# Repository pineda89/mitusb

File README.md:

# mitusb

A USB bridge for Teensy 4.1 that sits between a mouse, keyboard or gamepad and the computer. Connect the device to J6 and the computer to the micro-USB port. At startup, the board copies the device's USB identity and descriptors and then passes everything through in both directions. If there is nothing it can copy, it becomes a generic mouse.

The device works without Ethernet. With a mouse, the network client can also read events and send pointer commands; keyboards and gamepads are passed through untouched. Use a trusted network because the UDP protocol has no authentication. [Profiles, limits, and hardware checks](firmware/README.md)

## Build, test, and upload

Install PlatformIO Core and make sure `pio` is on your PATH. The first build downloads the toolchain and libraries. GNU Make is optional. The client requires Python 3.7 or later. You can run the native tests and build the firmware without a board.

Run the relevant command from the repository root.

```sh
make test    # Run the native tests
make         # Build the firmware
make upload  # Build and flash the board
make clean   # Remove the Teensy build output
```

The build produces `firmware/.pio/build/teensy41/firmware.hex`. Keep the device connected to J6 during restart so the firmware can capture its descriptors. If the loader cannot find the Teensy, press its **Program** button once.

The equivalent PlatformIO commands run from the firmware directory.

```sh
cd firmware
pio test -e native
pio run -e teensy41
pio run -e teensy41 -t upload
pio run -e teensy41 -t clean
```

## Directories

| Directory | Contents |
|---|---|
| [firmware/](firmware/) | Firmware, UDP protocol, and hardware checks |
| [client/](client/) | Command-line client and usage examples |
| [hardware/](hardware/) | KiCad project and board fabrication files |

## License

The project uses the [MIT License](LICENSE). The third-party KiCad libraries have [separate terms](hardware/README.md).

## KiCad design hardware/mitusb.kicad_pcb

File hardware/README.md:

# hardware

Carrier PCB for the Teensy 4.1, designed in KiCad 9.

## Contents

| Path | What |
|---|---|
| `mitusb.kicad_pro` | KiCad project (schematic + PCB) |
| `library/` | Project-local symbols, footprints and 3D models |
| `production/Gerber.zip` | Gerbers and drill files |
| `production/BOM.csv` | Bill of materials with LCSC part numbers |
| `production/mitusb-all-pos.csv` | Pick-and-place positions |
| `renders/` | Renders of the bare PCB and with the Teensy fitted |
| `enclosure/mitusb-case.scad` | Parametric OpenSCAD enclosure: base and flat lid, four M3 screws |
| `enclosure/mitusb-base.stl`, `enclosure/mitusb-lid.stl` | Printable exports of the enclosure |
| `enclosure/renders/` | Renders of the enclosure |

## Parts

| Ref | Part |
|---|---|
| U1 | Teensy 4.1, socketed on two 1x24 2.54 mm headers (J3, J4) |
| J6 | USB-A receptacle (USB host port, for the mouse/keyboard) |
| J5 | HanRun HY931147C RJ45 with magnetics (Teensy Ethernet) |
| J1 | 2x03 2.00 mm socket (Teensy Ethernet header) |
| J2 | 1x05 2.54 mm socket (Teensy USB host header) |
| C1 | 100 nF |
| H1-H4 | M3 mounting holes |

Mount the Teensy with its micro-USB end towards the `<- USB` mark on the
silkscreen.

## Ordering

The production files are in JLCPCB format: upload `Gerber.zip`, then `BOM.csv`
and `mitusb-all-pos.csv` for assembly.

## Third-party libraries

The Teensy 4.1 (SparkFun DEV-16771) and HY931147C symbols, footprints and STEP
models in `library/` come from [SnapEDA](https://www.snapeda.com) and are
subject to [SnapEDA's terms](https://www.snapeda.com/about/terms/).

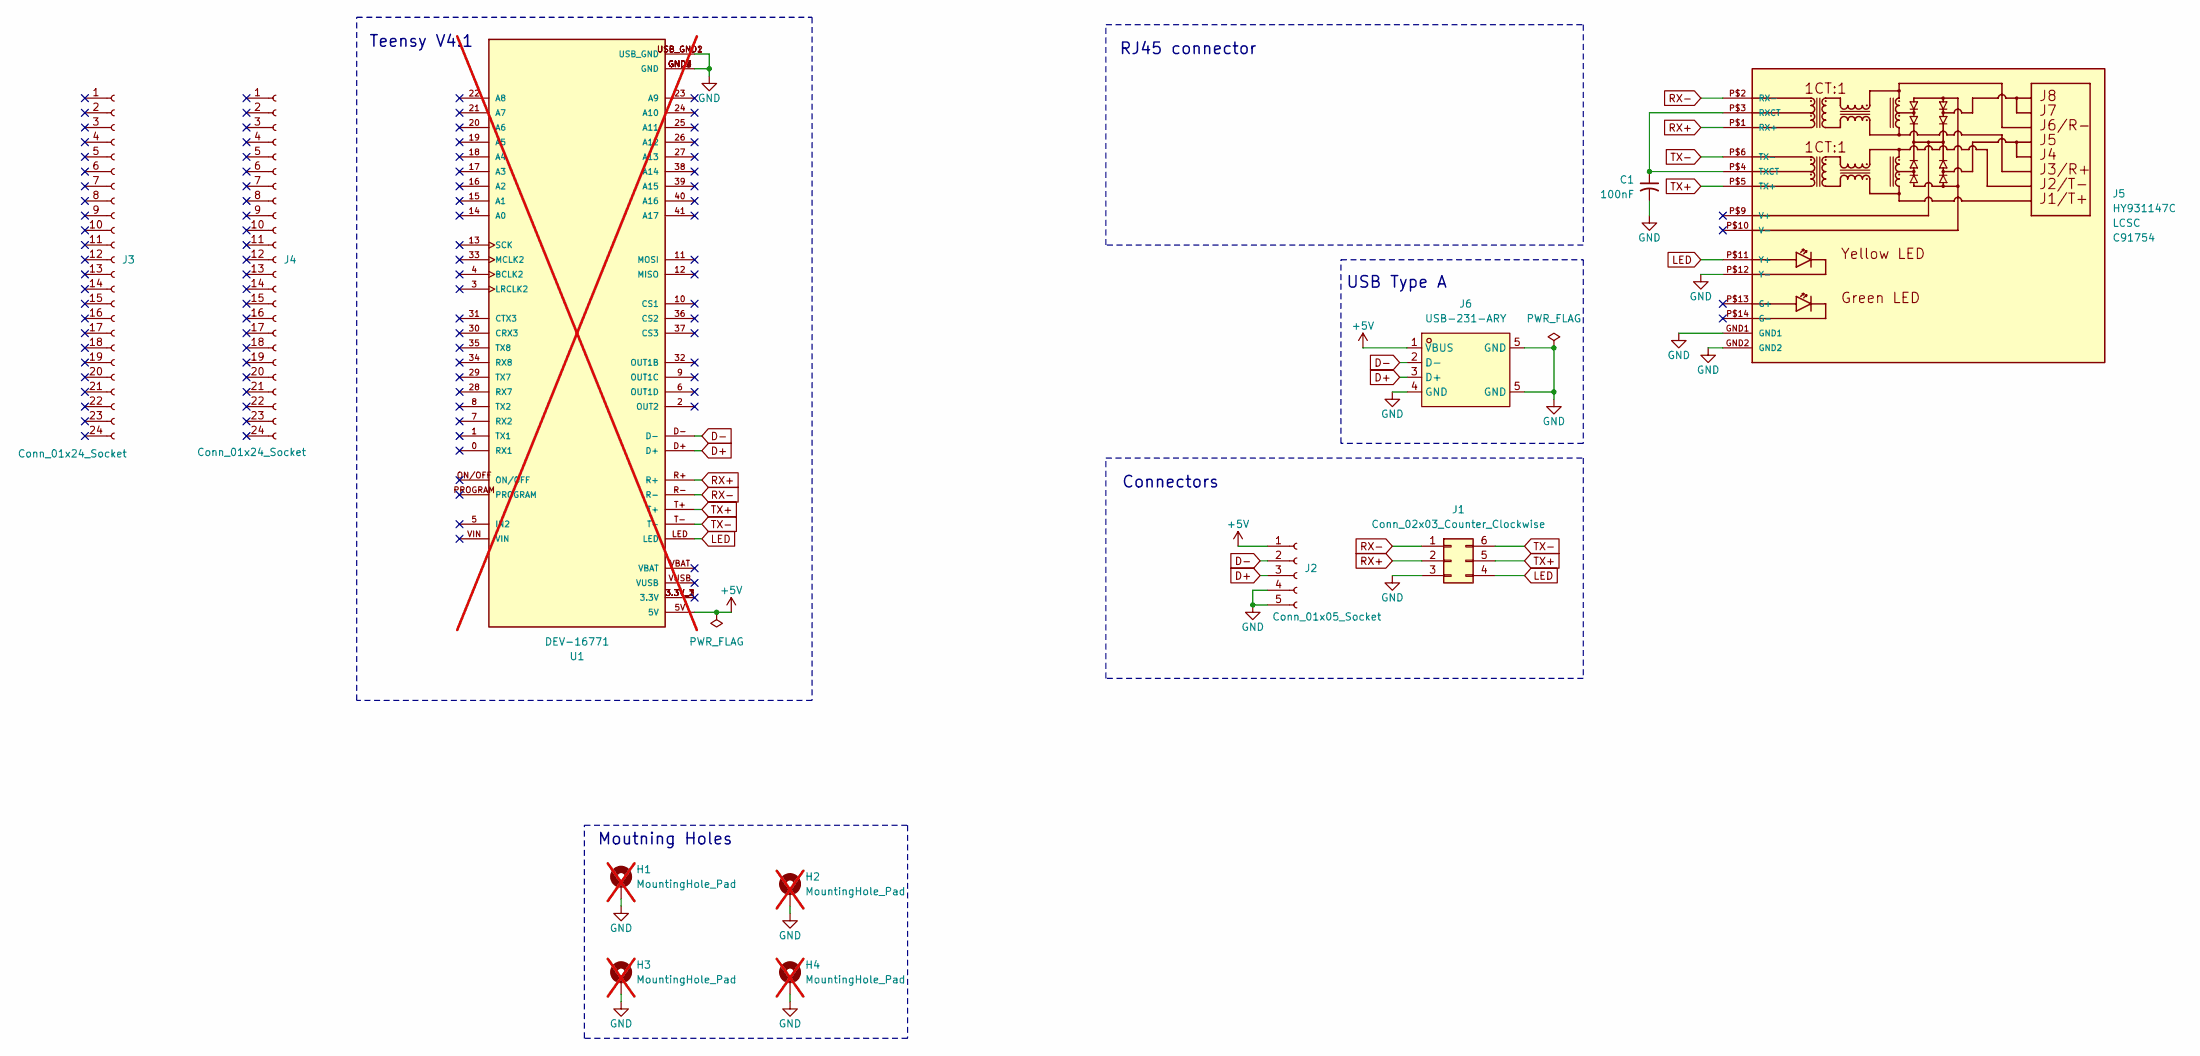
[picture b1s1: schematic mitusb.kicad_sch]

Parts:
C1: 100nF; CP_EIA-3216-10_Kemet-I
H1, H2, H3, H4: MountingHole_Pad; MountingHole_3.2mm_M3_DIN965_Pad_TopBottom; not fitted
J1: Conn_02x03_Counter_Clockwise; PinSocket_2x03_P2.00mm_Vertical
J2: Conn_01x05_Socket; PinSocket_1x05_P2.54mm_Vertical
J3, J4: Conn_01x24_Socket; PinSocket_1x24_P2.54mm_Vertical
J5: HY931147C
J6: USB-231-ARY; USB_A_Stewart_SS-52100-001_Horizontal
U1: DEV-16771; teensy 4.1; PARTREV 4.1; not fitted

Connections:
+5V: J2.1, J6.1 (VBUS), U1.5V
D+: J2.3, J6.3 (D+), U1.D+
D-: J2.2, J6.2 (D-), U1.D-
GND: C1.2, H1.1, H2.1, H3.1, H4.1, J1.3, J2.4, J2.5, J5.GND1, J5.GND2, J5.P$12 (Y-), J6.4 (GND), J6.5 (GND), U1.GND1 (GND), U1.GND2 (GND), U1.GND3 (GND), U1.GND4 (GND), U1.GND5 (GND), U1.USB_GND1 (USB_GND), U1.USB_GND2 (USB_GND)
LED: J1.4, J5.P$11 (Y+), U1.LED
unnamed: C1.1, J5.P$3 (RXCT), J5.P$4 (TXCT)
unnamed: U1.3.3V_1 (3.3V), U1.3.3V_2 (3.3V), U1.3.3V_3 (3.3V)
RX+: J1.2, J5.P$1 (RX+), U1.R+
RX-: J1.1, J5.P$2 (RX-), U1.R-
TX+: J1.5, J5.P$5 (TX+), U1.T+
TX-: J1.6, J5.P$6 (TX-), U1.T-

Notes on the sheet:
RJ45 connector
Moutning Holes
Teensy V4.1
USB Type A
Connectors

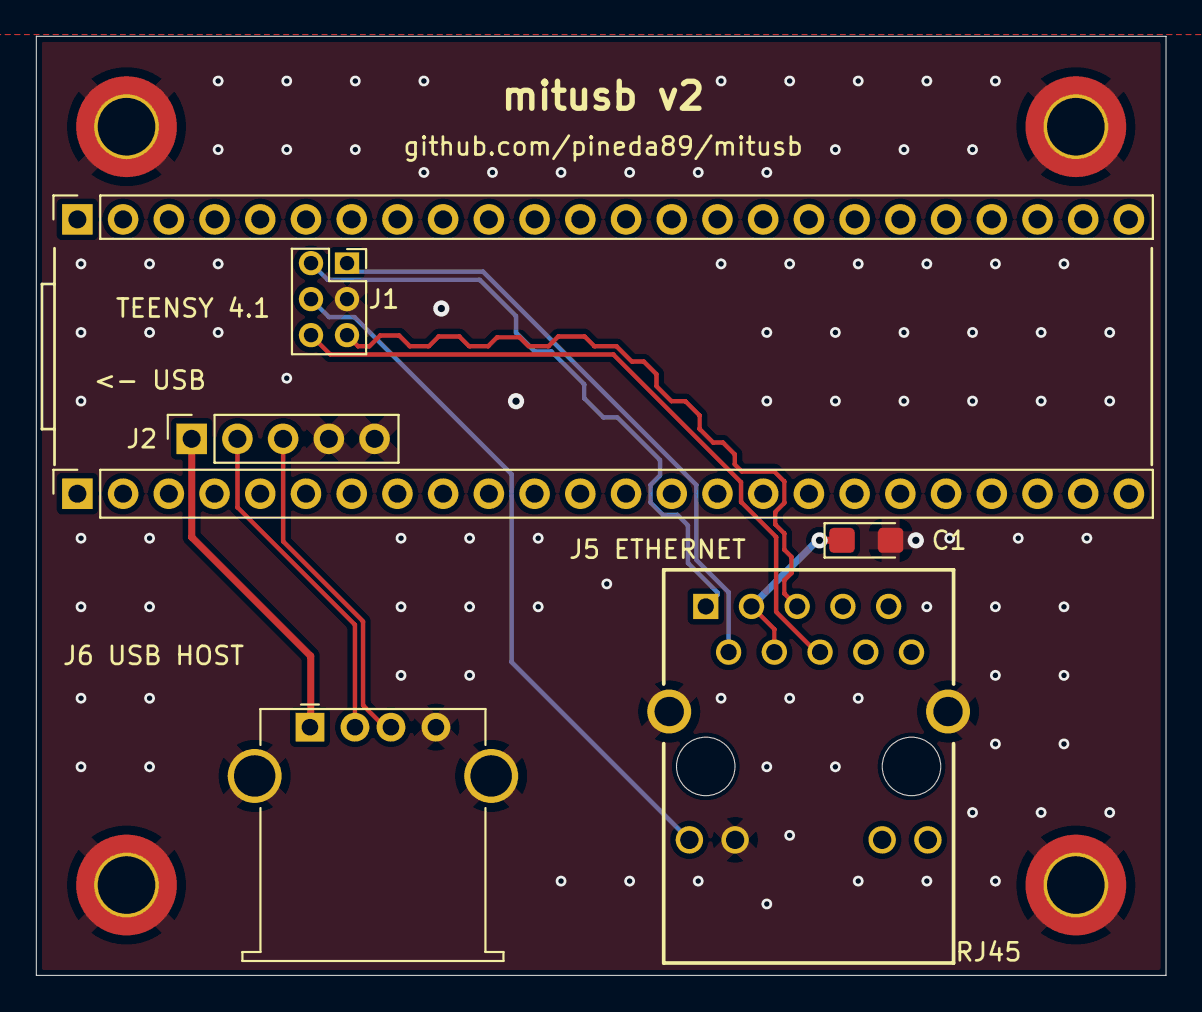
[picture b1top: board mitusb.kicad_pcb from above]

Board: 2 copper layers, 62.8 x 52.2 mm, 11 parts (0 on the bottom side), 10 nets.

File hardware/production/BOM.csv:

"Designator","Value","Footprint","Quantity","Supplier","Supplier Part Number"
"C1","100nF","Capacitor_Tantalum_SMD:CP_EIA-3216-10_Kemet-I","1","LCSC","C7173"
"J2","Conn_01x05_Socket","Connector_PinSocket_2.54mm:PinSocket_1x05_P2.54mm_Vertical","1","LCSC","C50950"
"J5","HY931147C","HY931147C:HY931147C","1","LCSC","C91754"
"J6","USB-231-ARY","Connector_USB:USB_A_Stewart_SS-52100-001_Horizontal","1","LCSC","C2880666"
"J3,J4","Conn_01x24_Socket","Connector_PinSocket_2.54mm:PinSocket_1x24_P2.54mm_Vertical","2","LCSC","C2883741"
"J1","Conn_02x03_Counter_Clockwise","Connector_PinSocket_2.00mm:PinSocket_2x03_P2.00mm_Vertical","1","LCSC","C7499367"
